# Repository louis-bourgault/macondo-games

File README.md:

# ferretboard!!!

> [!IMPORTANT]
> # PLEASE READ
> The primary documentation for this project can be found at [ferretboard.louisbourgault.com/docs](https://ferretboard.louisbourgault.com/docs). Please read from that source for organised information on software interfaces, assembly, and a more complete project overview.
> 
> This README remains the authoritative source on commands to build the firmware for the device, and also has a nice image gallery at the end.

# What is this?
Ferretboard is a simple games console, made to be easy to program and cheap to produce. Version one uses a RP2040 MCU; version two, currently in development, upgrades this to the RP2350 and changes the form factor significantly. The display is a 240x240 1.54" LCD, which is common and cost effective. It is battery powered, using a basic 3.7v LiPo.

The idea for this project, in the long term, is to be an easy introduction to programming and game development for students. The micropython sdk is editable in web, easy to get started using, and would be perfect in the long run for a classroom setting or Hack Club larger program. The upgrade to the RP2350 will make this level of software possible, with more RAM and processing power to make running complicated games within Micropython possible. 

The overall dimensions of the build are around 100x50mm for both v1 and v2, with a depth of around 20mm. The case is 3d printed.

This is made as a part of Hack Club Macondo. You can find my project at [macondo.hackclub.com/projects/1137](https://macondo.hackclub.com/projects/1137). Thank you to Hack Club for financing and helping me with this project. You can find all acknowledgements for this project at [ferretboard.louisbourgault.com/thanks](https://ferretboard.louisbourgault.com/thanks)

## Online stuff!
Docs site and main site: [ferretboard.louisbourgault.com](https://ferretboard.louisbourgault.com)
Web editor for the micropython sdk: [editor.louisbourgault.com](https://editor.louisbourgault.com)

## Project Structure
See at [ferretboard.louisbourgault.com/docs/structure](https://ferretboard.louisbourgault.com/docs/structure)

# Building Firmware
There's quite a few different firmwares at this point to build. Docs on how to do each of them:

[Original Go System](https://ferretboard.louisbourgault.com/docs/go-building)
[New micropython system (embedded into Go)](https://ferretboard.louisbourgault.com/docs/micropython-building)
[Old micropython system](https://ferretboard.louisbourgault.com/docs/oldmp-build)

To flash firmware on v2, hold down the reset button and reboot the device. On v1, manually short QSPI_SS and GND with tweezers and then reboot. The easiest access points for this are the first and last pins of the flash chip on the top side - you can just pinch the top of the flash chip, and that should do it.

Then, either use picotool over command line, or just drag the uf2 file into the RPI-RP2 volume that shows up in Finder/File Explorer/Dolphin/whatever you use.

# Assembly instructions
Assembly instructions can be found at [ferretboard.louisbourgault.com/docs/assembly](https://ferretboard.louisbourgault.com/docs/assembly).

# Gallery

The full gallery can be found at [ferretboard.louisbourgault.com/gallery](https://ferretboard.louisbourgault.com/gallery). Here is just a few sample images: 

## The micropython online editor working!

## Finished Device (v1)

## Fusion design for new version (not produced yet)

# Acknowledgements

Find all acknowledgements at [ferretboard.louisbourgault.com/thanks](https://ferretboard.louisbourgault.com/thanks)

Font file used in /software/helpers/text.go - Public Domain, [github.com/dhepper/font8x8](https://github.com/dhepper/font8x8/blob/master/font8x8_basic.h)

framebuf2 - MIT Licenced, https://github.com/peter-l5/framebuf2

codemirror v6 - MIT Licenced, https://code.haverbeke.berlin/codemirror/dev/ 

# Licensing

This project is dual-licensed:
* **Hardware:** The schematic, PCB layout, and documentation files are licensed under the [CERN Open Hardware Licence v2 - Strongly Reciprocal (CERN-OHL-S-2.0)](./mini-games/LICENSE.txt). If you modify and distribute this hardware, you must share your changes to it. 
* **Firmware/Software:** All source code is licensed under the [GNU AGPLv3](./LICENSE.txt). You can't copy and distribute a changed version of this without making your modifications public, including distribution by serving a part of this code over a network. [Even if you're Bambu Labs.](https://consumerrights.wiki/w/Bambu_Lab_cease_and_desist_against_OrcaSlicer_fork_developer)

# Looking for something?
Looking for something, like assembly instructions or something else? Please check the link up the top of this readme.

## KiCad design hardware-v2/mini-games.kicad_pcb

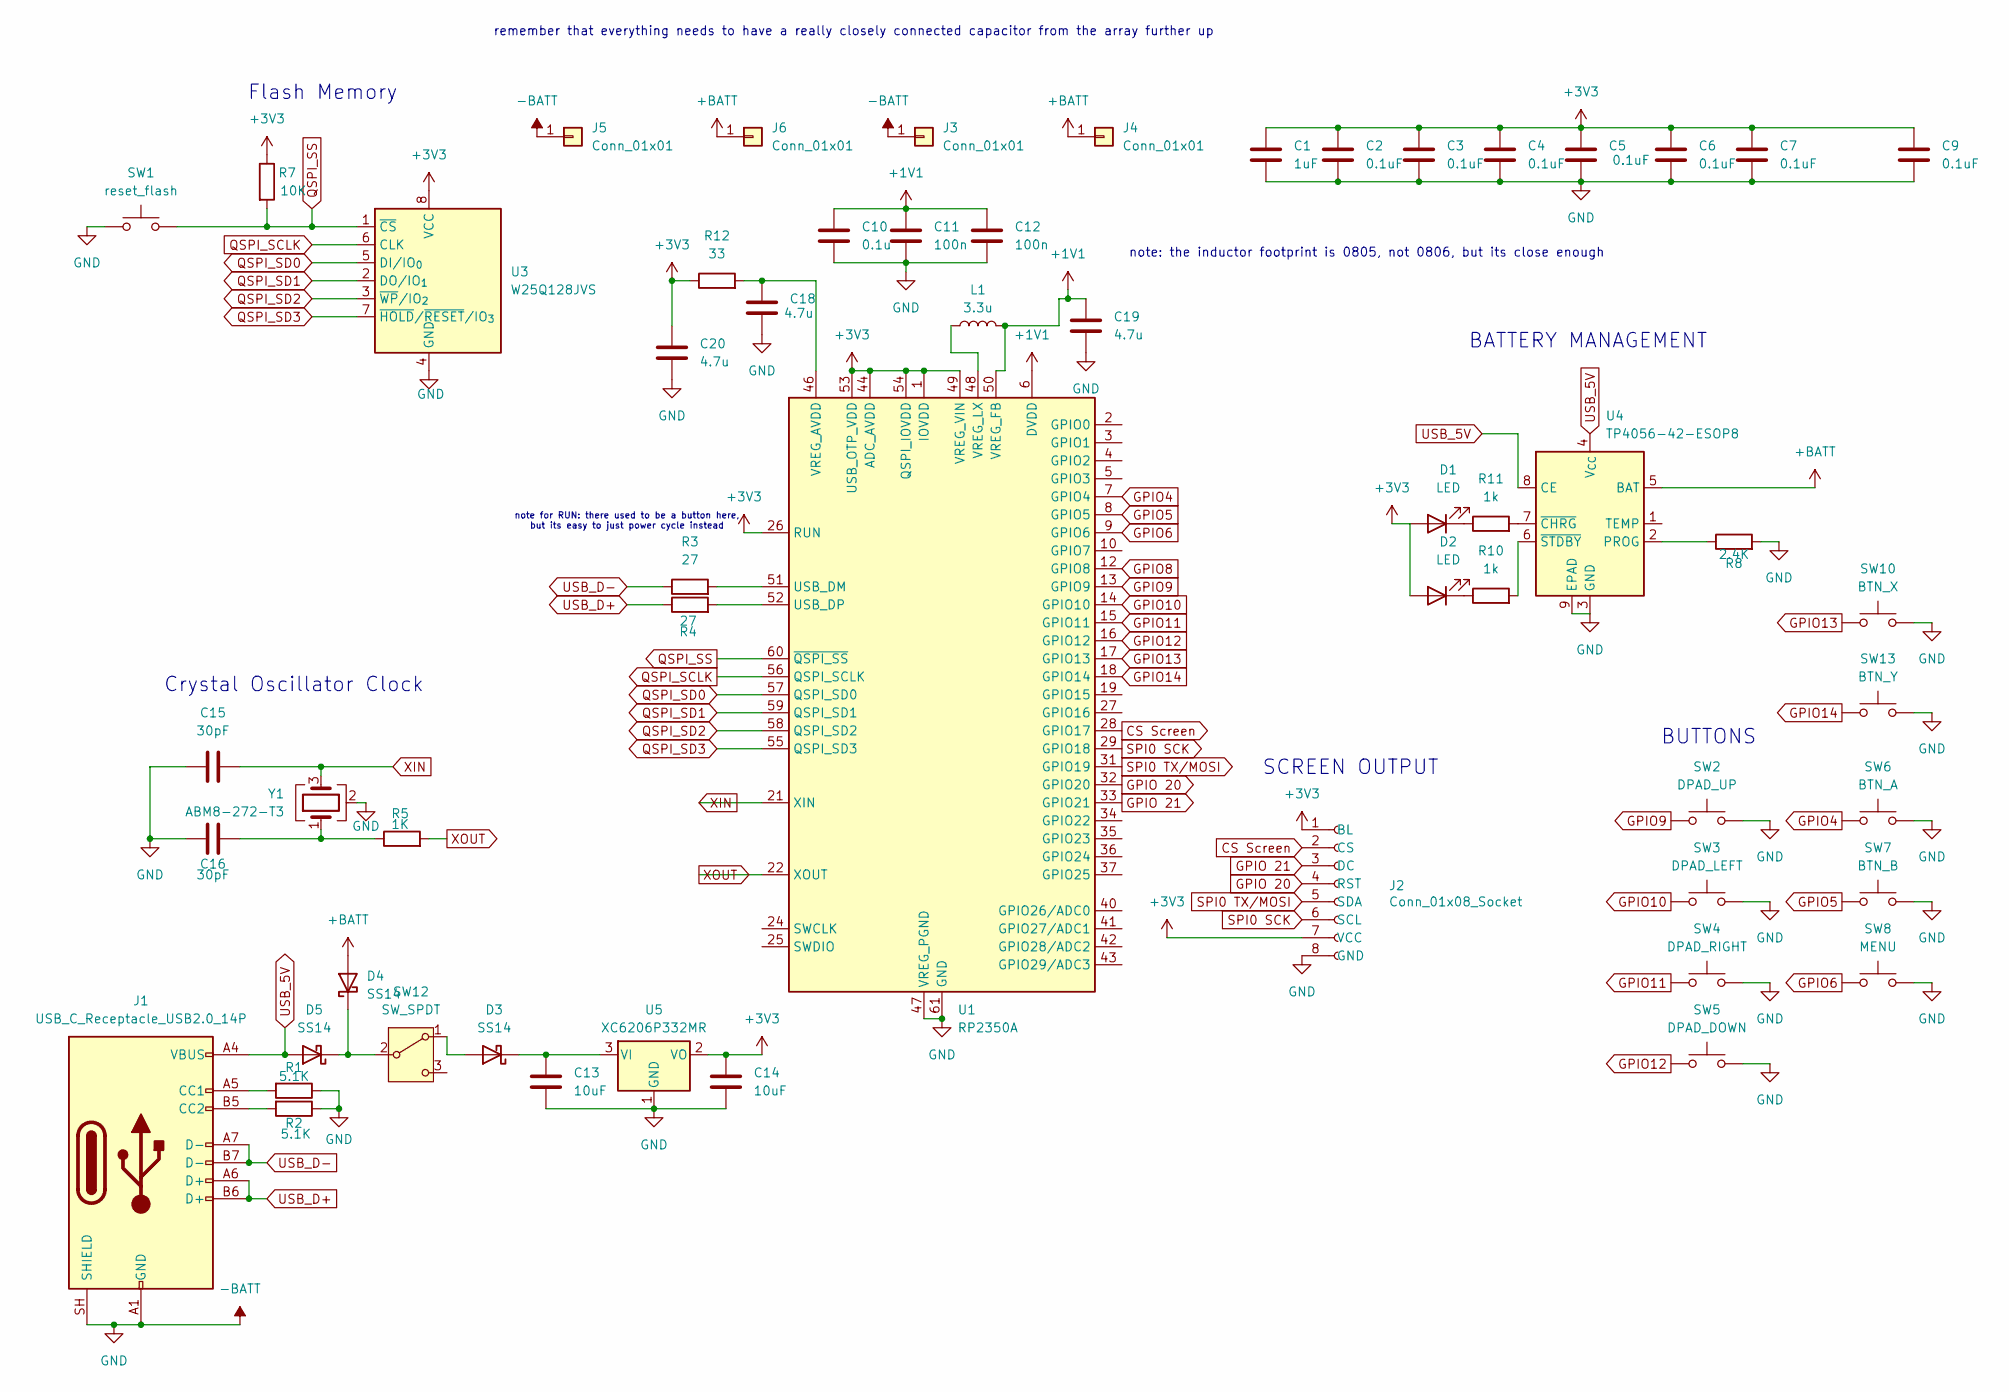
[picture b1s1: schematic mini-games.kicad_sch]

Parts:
C1: 1uF; C_0402_1005Metric
C2, C3, C4, C5, C6, C7, C9: 0.1uF; C_0402_1005Metric
C10: 0.1u; C_0402_1005Metric
C11, C12: 100n; C_0402_1005Metric
C13, C14: 10uF; C_0402_1005Metric
C15, C16: 30pF; C_0402_1005Metric
C18, C19, C20: 4.7u; C_0402_1005Metric
D1, D2: LED; LED_0603_1608Metric
D3, D4, D5: SS14; D_SOD-123
J1: USB_C_Receptacle_USB2.0_14P; USB_C_Receptacle_HRO_TYPE-C-31-M-12
J2: Conn_01x08_Socket; 1.54_ TFT Header
J3, J4, J5, J6: Conn_01x01; TestPoint_Pad_2.0x2.0mm
L1: 3.3u; L_0805_2012Metric
R1, R2: 5.1K; R_0402_1005Metric
R3, R4: 27; R_0402_1005Metric
R5: 1K; R_0402_1005Metric
R7: 10K; R_0402_1005Metric
R8: 2.4K; R_0402_1005Metric
R10, R11: 1k; R_0402_1005Metric
R12: 33; R_0402_1005Metric
SW1: reset_flash; SW_Push_SPST_NO_Alps_SKRK
SW2: DPAD_UP; SW_PUSH_6mm+6mm_Dual
SW3: DPAD_LEFT; SW_PUSH_6mm+6mm_Dual
SW4: DPAD_RIGHT; SW_PUSH_6mm+6mm_Dual
SW5: DPAD_DOWN; SW_PUSH_6mm+6mm_Dual
SW6: BTN_A; SW_PUSH_6mm+6mm_Dual
SW7: BTN_B; SW_PUSH_6mm+6mm_Dual
SW8: MENU; SW_PUSH_6mm+6mm_Dual
SW10: BTN_X; SW_PUSH_6mm+6mm_Dual
SW12: SW_SPDT; SW_SLIDE-3pin_2.54_1.2mm-hole
SW13: BTN_Y; SW_PUSH_6mm+6mm_Dual
U1: RP2350A; QFN-60-1EP_7x7mm_P0.4mm_EP3.4x3.4mm
U3: W25Q128JVS; SOIC-8_5.3x5.3mm_P1.27mm
U4: TP4056-42-ESOP8; SOIC-8-1EP_3.9x4.9mm_P1.27mm_EP2.41x3.3mm_ThermalVias
U5: XC6206P332MR; SOT-23-3
Y1: ABM8-272-T3; Crystal_SMD_3225-4Pin_3.2x2.5mm

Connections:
+1V1: C10.1, C11.1, C12.1, C19.1, L1.2, U1.6 (DVDD), U1.23 (DVDD), U1.39 (DVDD), U1.50 (VREG_FB)
+3V3: C1.1, C2.1, C3.1, C4.1, C5.1, C6.1, C7.1, C9.1, C14.1, C20.1, D1.2 (A), D2.2 (A), J2.1 (BL), J2.7 (VCC), R7.1, R12.1, U1.1 (IOVDD), U1.11 (IOVDD), U1.20 (IOVDD), U1.26 (RUN), U1.30 (IOVDD), U1.38 (IOVDD), U1.44 (ADC_AVDD), U1.45 (IOVDD), U1.49 (VREG_VIN), U1.53 (USB_OTP_VDD), U1.54 (QSPI_IOVDD), U3.8 (VCC), U5.2 (VO)
+BATT: D4.2 (A), J4.1 (Pin_1_1), J6.1 (Pin_1_1), U4.5 (BAT)
-BATT: C1.2, C2.2, C3.2, C4.2, C5.2, C6.2, C7.2, C9.2, C10.2, C11.2, C12.2, C13.2, C14.2, C15.1, C16.1, C18.2, C19.2, C20.2, J1.A1 (GND), J1.A12 (GND), J1.B1 (GND), J1.B12 (GND), J1.SH (SHIELD), J2.8 (GND), J3.1 (Pin_1_1), J5.1 (Pin_1_1), R1.1, R2.1, R8.2, SW1.1, SW2.2, SW3.2, SW4.2, SW5.2, SW6.2, SW7.2, SW8.2, SW10.2, SW13.2, U1.47 (VREG_PGND), U1.61 (GND), U3.4 (GND), U4.3 (GND), U4.9 (EPAD), U5.1 (GND), Y1.2 (G), Y1.4 (G)
CS Screen: J2.2 (CS), U1.28 (GPIO17)
GPIO4: SW6.1, U1.7 (GPIO4)
GPIO5: SW7.1, U1.8 (GPIO5)
GPIO6: SW8.1, U1.9 (GPIO6)
GPIO8: U1.12 (GPIO8)
GPIO9: SW2.1, U1.13 (GPIO9)
GPIO10: SW3.1, U1.14 (GPIO10)
GPIO11: SW4.1, U1.15 (GPIO11)
GPIO12: SW5.1, U1.16 (GPIO12)
GPIO13: SW10.1, U1.17 (GPIO13)
GPIO14: SW13.1, U1.18 (GPIO14)
GPIO 20: J2.4 (RST), U1.32 (GPIO20)
GPIO 21: J2.3 (DC), U1.33 (GPIO21)
unnamed: C16.2, R5.1, Y1.1
unnamed: D1.1 (K), R11.1
unnamed: D2.1 (K), R10.1
unnamed: D3.2 (A), SW12.1 (A)
unnamed: C13.1, D3.1 (K), U5.3 (VI)
unnamed: D4.1 (K), D5.1 (K), SW12.2 (B)
unnamed: J1.A5 (CC1), R1.2
unnamed: J1.B5 (CC2), R2.2
unnamed: R3.2, U1.51 (USB_DM)
unnamed: R4.2, U1.52 (USB_DP)
unnamed: C18.1, R12.2, U1.46 (VREG_AVDD)
unnamed: L1.1, U1.48 (VREG_LX)
unnamed: R8.1, U4.2 (PROG)
unnamed: R11.2, U4.7 (~CHRG)
unnamed: R10.2, U4.6 (~STDBY)
QSPI_SCLK: U1.56 (QSPI_SCLK), U3.6 (CLK)
QSPI_SD0: U1.57 (QSPI_SD0), U3.5 (DI/IO_{0})
QSPI_SD1: U1.59 (QSPI_SD1), U3.2 (DO/IO_{1})
QSPI_SD2: U1.58 (QSPI_SD2), U3.3 (~WP/IO_{2})
QSPI_SD3: U1.55 (QSPI_SD3), U3.7 (~HOLD/~RESET/IO_{3})
QSPI_SS: R7.2, SW1.2, U1.60 (~QSPI_SS), U3.1 (~CS)
SPI0 SCK: J2.6 (SCL), U1.29 (GPIO18)
SPI0 TX/MOSI: J2.5 (SDA), U1.31 (GPIO19)
USB_5V: D5.2 (A), J1.A4 (VBUS), J1.A9 (VBUS), J1.B4 (VBUS), J1.B9 (VBUS), U4.4 (V_{CC}), U4.8 (CE)
USB_D+: J1.A6 (D+), J1.B6 (D+), R4.1
USB_D-: J1.A7 (D-), J1.B7 (D-), R3.1
XIN: C15.2, U1.21 (XIN), Y1.3
XOUT: R5.2, U1.22 (XOUT)

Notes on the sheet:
SCREEN OUTPUT
note for RUN: there used to be a button here, but its easy to just power cycle instead
Flash Memory
BATTERY MANAGEMENT
remember that everything needs to have a really closely connected capacitor from the array further up
BUTTONS
Crystal Oscillator Clock
note: the inductor footprint is 0805, not 0806, but its close enough

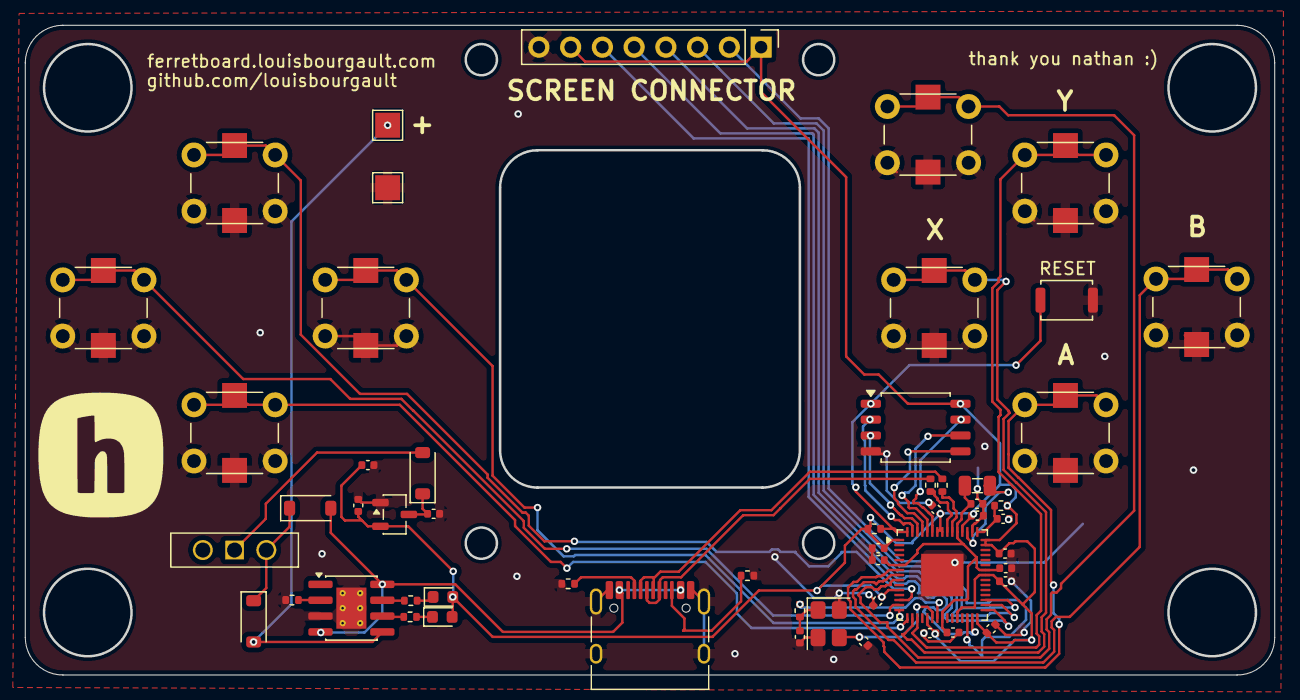
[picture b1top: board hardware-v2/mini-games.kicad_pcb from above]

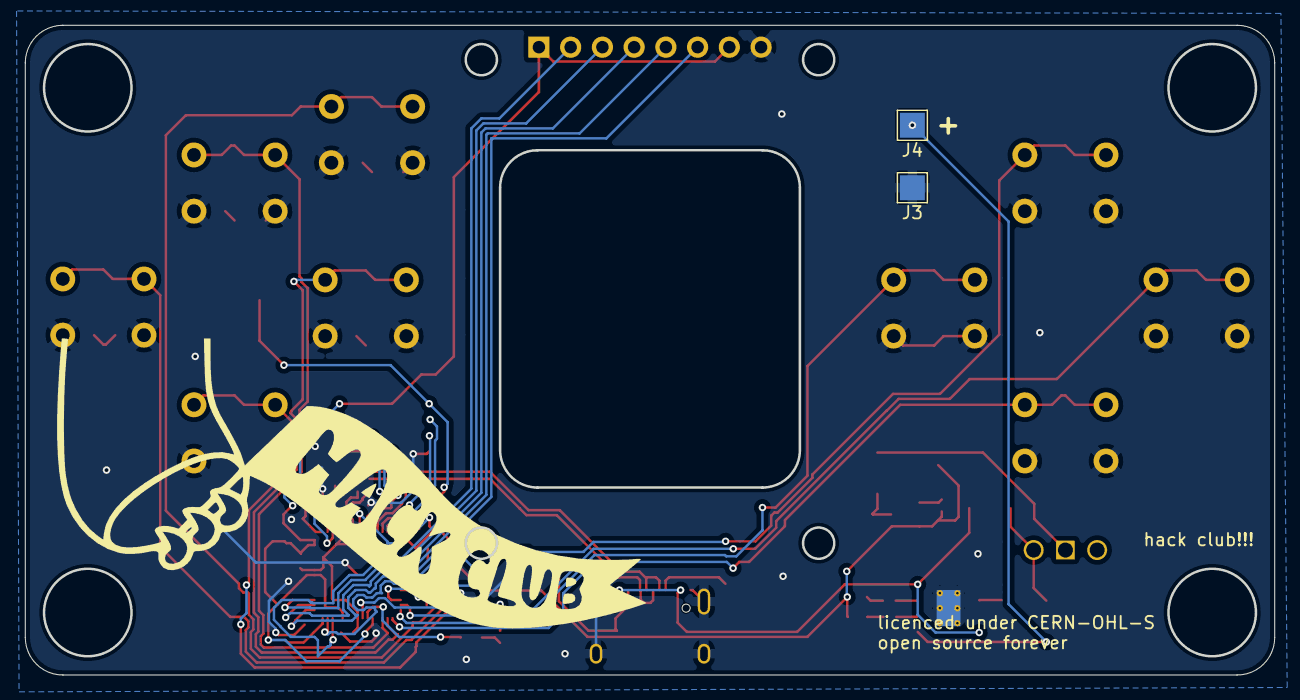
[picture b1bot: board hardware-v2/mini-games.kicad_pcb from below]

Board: 2 copper layers, 100.0 x 52.0 mm, 56 parts (2 on the bottom side), 44 nets.

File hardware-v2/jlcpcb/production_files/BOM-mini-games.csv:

Comment,Designator,Footprint,LCSC,Quantity
0.1u,C10,C_0402_1005Metric,C1525,1
0.1uF,"C2,C3,C4,C5,C6,C7,C9",C_0402_1005Metric,C1525,7
100n,"C11,C12",C_0402_1005Metric,C1525,2
10K,R7,R_0402_1005Metric,C25744,1
10uF,"C13,C14",C_0402_1005Metric,C15525,2
15pF,"C15,C16",C_0402_1005Metric,C1548,2
1K,R5,R_0402_1005Metric,C11702,1
1k,"R10,R11",R_0402_1005Metric,C11702,2
1uF,C1,C_0402_1005Metric,C52923,1
2.4K,R8,R_0402_1005Metric,C25882,1
27,"R3,R4",R_0402_1005Metric,C2909343,2
3.3u,L1,L_0806_2016Metric,C42411119,1
33,R12,R_0402_1005Metric,C25105,1
4.7u,"C18,C19,C20",C_0402_1005Metric,C23733,3
5.1K,"R1,R2",R_0402_1005Metric,C25905,2
ABM8-272-T3,Y1,Crystal_SMD_3225-4Pin_3.2x2.5mm,C20625731,1
LED,D1,LED_0603_1608Metric,C2286,1
LED,D2,LED_0603_1608Metric,C2290,1
RP2350A,U1,QFN-60-1EP_7x7mm_P0.4mm_EP3.4x3.4mm,C42411118,1
SS14,"D3,D4,D5",D_SOD-123,C49023418,3
TP4056-42-ESOP8,U4,SOIC-8-1EP_3.9x4.9mm_P1.27mm_EP2.41x3.3mm_ThermalVias,C16581,1
USB_C_Receptacle_USB2.0_14P,J1,USB_C_Receptacle_HRO_TYPE-C-31-M-12,C165948,1
W25Q128JVS,U3,SOIC-8_5.3x5.3mm_P1.27mm,C97521,1
XC6206P332MR,U5,SOT-23-3,C5446,1
reset_flash,SW1,SW_Push_SPST_NO_Alps_SKRK,C720477,1
DPAD_DOWN,SW5,SW_PUSH_6mm+6mm_Dual,,1
BTN_B,SW7,SW_PUSH_6mm+6mm_Dual,,1
BTN_A,SW6,SW_PUSH_6mm+6mm_Dual,,1
BTN_X,SW10,SW_PUSH_6mm+6mm_Dual,,1
DPAD_UP,SW2,SW_PUSH_6mm+6mm_Dual,,1
DPAD_RIGHT,SW4,SW_PUSH_6mm+6mm_Dual,,1
BTN_Y,SW13,SW_PUSH_6mm+6mm_Dual,,1
DPAD_LEFT,SW3,SW_PUSH_6mm+6mm_Dual,,1
MENU,SW8,SW_PUSH_6mm+6mm_Dual,,1
Conn_01x08_Socket,J2,1.54_ TFT Header,,1
Conn_01x01,J4,TestPoint_Pad_2.0x2.0mm,,1
SW_SPDT,SW12,SW_SLIDE-3pin_2.54_1.2mm-hole,,1
Conn_01x01,J3,TestPoint_Pad_2.0x2.0mm,,1
Conn_01x01,J5,TestPoint_Pad_2.0x2.0mm,,1
Conn_01x01,J6,TestPoint_Pad_2.0x2.0mm,,1

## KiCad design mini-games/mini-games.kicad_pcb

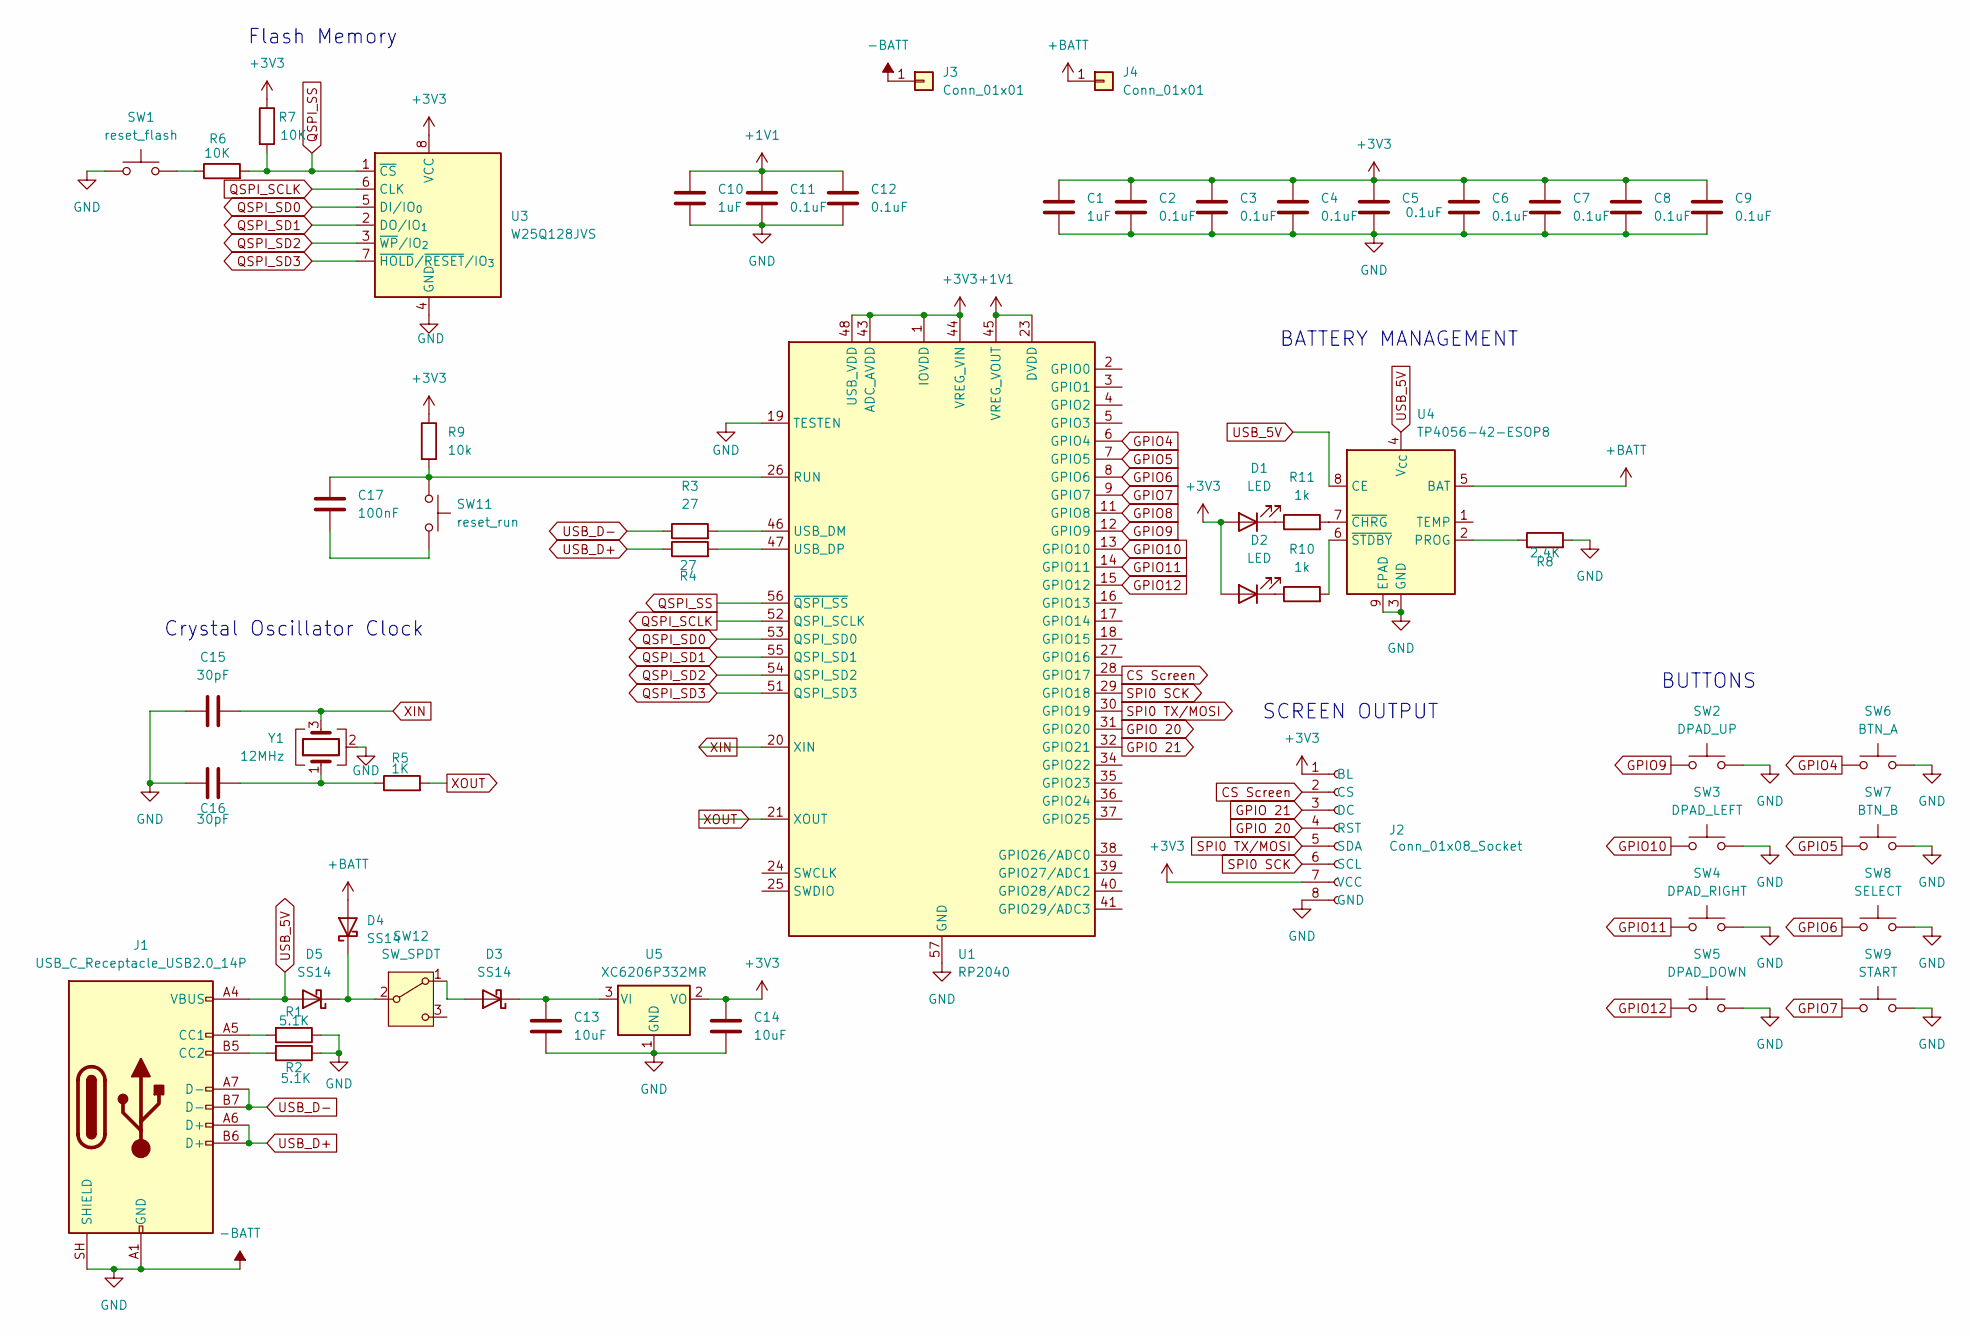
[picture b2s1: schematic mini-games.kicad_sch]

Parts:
C1, C10: 1uF; C_0402_1005Metric
C2, C3, C4, C5, C6, C7, C8, C9, C11, C12: 0.1uF; C_0402_1005Metric
C13, C14: 10uF; C_0402_1005Metric
C15, C16: 30pF; C_0402_1005Metric
C17: 100nF; C_0402_1005Metric
D1, D2: LED; LED_0603_1608Metric
D3, D4, D5: SS14; D_SOD-123
J1: USB_C_Receptacle_USB2.0_14P; USB_C_Receptacle_HRO_TYPE-C-31-M-12
J2: Conn_01x08_Socket; PinHeader_1x08_P2.54mm_Vertical
J3, J4: Conn_01x01; TestPoint_Pad_2.0x2.0mm
R1, R2: 5.1K; R_0402_1005Metric
R3, R4: 27; R_0402_1005Metric
R5: 1K; R_0402_1005Metric
R6, R7: 10K; R_0402_1005Metric
R8: 2.4K; R_0402_1005Metric
R9: 10k; R_0402_1005Metric
R10, R11: 1k; R_0402_1005Metric
SW1: reset_flash; SW_Push_SPST_NO_Alps_SKRK
SW2: DPAD_UP; SW_PUSH_6mm
SW3: DPAD_LEFT; SW_PUSH_6mm
SW4: DPAD_RIGHT; SW_PUSH_6mm
SW5: DPAD_DOWN; SW_PUSH_6mm
SW6: BTN_A; SW_PUSH_6mm
SW7: BTN_B; SW_PUSH_6mm
SW8: SELECT; SW_Push_SPST_NO_Alps_SKRK
SW9: START; SW_Push_SPST_NO_Alps_SKRK
SW11: reset_run; SW_Push_SPST_NO_Alps_SKRK
SW12: SW_SPDT; SW_SPDT_Shouhan_MSK12C02
U1: RP2040; QFN-56-1EP_7x7mm_P0.4mm_EP3.2x3.2mm
U3: W25Q128JVS; SOIC-8_5.3x5.3mm_P1.27mm
U4: TP4056-42-ESOP8; SOIC-8-1EP_3.9x4.9mm_P1.27mm_EP2.41x3.3mm_ThermalVias
U5: XC6206P332MR; SOT-23-3
Y1: 12MHz; Crystal_SMD_3225-4Pin_3.2x2.5mm

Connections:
+1V1: C10.1, C11.1, C12.1, U1.23 (DVDD), U1.45 (VREG_VOUT), U1.50 (DVDD)
+3V3: C1.1, C2.1, C3.1, C4.1, C5.1, C6.1, C7.1, C8.1, C9.1, C14.1, D1.2 (A), D2.2 (A), J2.1 (BL), J2.7 (VCC), R7.1, R9.1, U1.1 (IOVDD), U1.10 (IOVDD), U1.22 (IOVDD), U1.33 (IOVDD), U1.42 (IOVDD), U1.43 (ADC_AVDD), U1.44 (VREG_VIN), U1.48 (USB_VDD), U1.49 (IOVDD), U3.8 (VCC), U5.2 (VO)
+BATT: D4.2 (A), J4.1 (Pin_1_1), U4.5 (BAT)
-BATT: C1.2, C2.2, C3.2, C4.2, C5.2, C6.2, C7.2, C8.2, C9.2, C10.2, C11.2, C12.2, C13.2, C14.2, C15.1, C16.1, J1.A1 (GND), J1.A12 (GND), J1.B1 (GND), J1.B12 (GND), J1.SH (SHIELD), J2.8 (GND), J3.1 (Pin_1_1), R1.1, R2.1, R8.2, SW1.1, SW2.2, SW3.2, SW4.2, SW5.2, SW6.2, SW7.2, SW8.2, SW9.2, SW12.SH, U1.19 (TESTEN), U1.57 (GND), U3.4 (GND), U4.3 (GND), U4.9 (EPAD), U5.1 (GND), Y1.2 (G), Y1.4 (G)
CS Screen: J2.2 (CS), U1.28 (GPIO17)
GPIO4: SW6.1, U1.6 (GPIO4)
GPIO5: SW7.1, U1.7 (GPIO5)
GPIO6: SW8.1, U1.8 (GPIO6)
GPIO7: SW9.1, U1.9 (GPIO7)
GPIO8: U1.11 (GPIO8)
GPIO9: SW2.1, U1.12 (GPIO9)
GPIO10: SW3.1, U1.13 (GPIO10)
GPIO11: SW4.1, U1.14 (GPIO11)
GPIO12: SW5.1, U1.15 (GPIO12)
GPIO 20: J2.4 (RST), U1.31 (GPIO20)
GPIO 21: J2.3 (DC), U1.32 (GPIO21)
unnamed: C16.2, R5.1, Y1.1
unnamed: C17.2, SW11.2
unnamed: D1.1 (K), R11.1
unnamed: D2.1 (K), R10.1
unnamed: D3.2 (A), SW12.1 (A)
unnamed: C13.1, D3.1 (K), U5.3 (VI)
unnamed: D4.1 (K), D5.1 (K), SW12.2 (B)
unnamed: J1.A5 (CC1), R1.2
unnamed: J1.B5 (CC2), R2.2
unnamed: R6.1, SW1.2
unnamed: C17.1, R9.2, SW11.1, U1.26 (RUN)
unnamed: R3.2, U1.46 (USB_DM)
unnamed: R4.2, U1.47 (USB_DP)
unnamed: R8.1, U4.2 (PROG)
unnamed: R11.2, U4.7 (~CHRG)
unnamed: R10.2, U4.6 (~STDBY)
QSPI_SCLK: U1.52 (QSPI_SCLK), U3.6 (CLK)
QSPI_SD0: U1.53 (QSPI_SD0), U3.5 (DI/IO_{0})
QSPI_SD1: U1.55 (QSPI_SD1), U3.2 (DO/IO_{1})
QSPI_SD2: U1.54 (QSPI_SD2), U3.3 (~WP/IO_{2})
QSPI_SD3: U1.51 (QSPI_SD3), U3.7 (~HOLD/~RESET/IO_{3})
QSPI_SS: R6.2, R7.2, U1.56 (~QSPI_SS), U3.1 (~CS)
SPI0 SCK: J2.6 (SCL), U1.29 (GPIO18)
SPI0 TX/MOSI: J2.5 (SDA), U1.30 (GPIO19)
USB_5V: D5.2 (A), J1.A4 (VBUS), J1.A9 (VBUS), J1.B4 (VBUS), J1.B9 (VBUS), U4.4 (V_{CC}), U4.8 (CE)
USB_D+: J1.A6 (D+), J1.B6 (D+), R4.1
USB_D-: J1.A7 (D-), J1.B7 (D-), R3.1
XIN: C15.2, U1.20 (XIN), Y1.3
XOUT: R5.2, U1.21 (XOUT)

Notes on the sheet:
SCREEN OUTPUT
Flash Memory
BATTERY MANAGEMENT
BUTTONS
Crystal Oscillator Clock

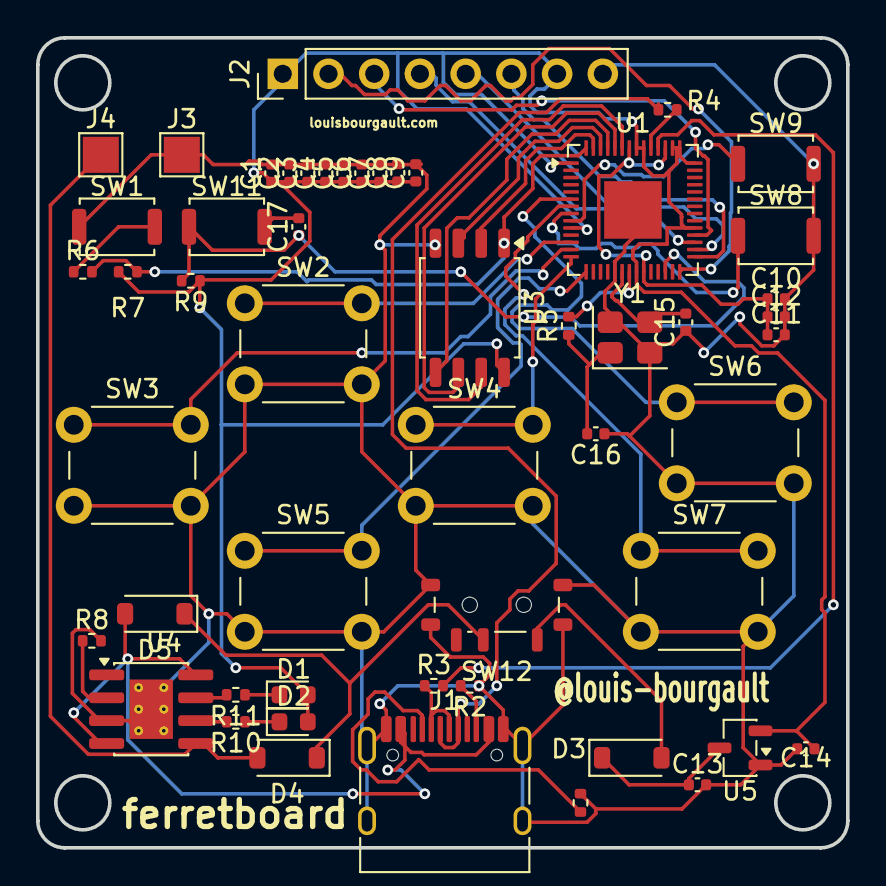
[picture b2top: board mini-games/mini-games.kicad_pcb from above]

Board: 2 copper layers, 45.0 x 45.0 mm, 53 parts (0 on the bottom side), 44 nets.

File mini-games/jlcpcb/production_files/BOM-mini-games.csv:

Comment,Designator,Footprint,LCSC,Quantity
0.1uF,"C11,C12,C2,C3,C4,C5,C6,C7,C8,C9",C_0402_1005Metric,C1525,10
100nF,C17,C_0402_1005Metric,C1525,1
10K,"R6,R7",R_0402_1005Metric,C25744,2
10k,R9,R_0402_1005Metric,C25744,1
10uF,"C13,C14",C_0402_1005Metric,C15525,2
12MHz,Y1,Crystal_SMD_3225-4Pin_3.2x2.5mm,C9002,1
1K,R5,R_0402_1005Metric,C11702,1
1k,"R10,R11",R_0402_1005Metric,C11702,2
1uF,"C1,C10",C_0402_1005Metric,C52923,2
2.4K,R8,R_0402_1005Metric,C25882,1
27,"R3,R4",R_0402_1005Metric,C25100,2
30pF,"C15,C16",C_0402_1005Metric,C1570,2
5.1K,"R1,R2",R_0402_1005Metric,C25905,2
LED,D1,LED_0603_1608Metric,C2286,1
LED,D2,LED_0603_1608Metric,C2290,1
POWER,SW10,SW_DIP_SPSTx01_Slide_Copal_CHS-01B_W7.62mm_P1.27mm,C3312309,1
RP2040,U1,QFN-56-1EP_7x7mm_P0.4mm_EP3.2x3.2mm,C2040,1
SELECT,SW8,SW_Push_SPST_NO_Alps_SKRK,C720477,1
SS14,"D3,D4,D5",D_SOD-123,C2480,3
START,SW9,SW_Push_SPST_NO_Alps_SKRK,C720477,1
TP4056-42-ESOP8,U4,SOIC-8-1EP_3.9x4.9mm_P1.27mm_EP2.41x3.3mm_ThermalVias,C16581,1
USB_C_Receptacle_USB2.0_14P,J1,USB_C_Receptacle_HRO_TYPE-C-31-M-12,C165948,1
W25Q128JVS,U3,SOIC-8_5.3x5.3mm_P1.27mm,C97521,1
XC6206P332MR,U5,SOT-23-3,C5446,1
reset_flash,SW1,SW_Push_SPST_NO_Alps_SKRK,C720477,1
reset_run,SW11,SW_Push_SPST_NO_Alps_SKRK,C720477,1
DPAD_DOWN,SW5,SW_PUSH_6mm,,1
DPAD_LEFT,SW3,SW_PUSH_6mm,,1
DPAD_UP,SW2,SW_PUSH_6mm,,1
DPAD_RIGHT,SW4,SW_PUSH_6mm,,1
BTN_B,SW7,SW_PUSH_6mm,,1
Conn_01x01,J4,TestPoint_Pad_2.0x2.0mm,,1
Conn_01x01,J3,TestPoint_Pad_2.0x2.0mm,,1
BTN_A,SW6,SW_PUSH_6mm,,1
Conn_01x08_Socket,J2,PinHeader_1x08_P2.54mm_Vertical,,1

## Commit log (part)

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2026-05-04 added files
2026-05-04 add readme
2026-05-07 finish schematic, start pcb
2026-05-07 edit pcb, layout things and change footprints yet again
2026-05-09 added gitignore
2026-05-09 categorised parts on pcb; changed one or two footprints, general improvements
2026-05-09 added backup files
2026-05-10 Finalised feature placements and routed PCB. Yet to fix errors given by DRC
2026-05-10 fixed drc critical problems
2026-05-10 added text
2026-05-11 updated, fixed more errors, ready for review i beleive!
2026-05-11 sorry, need to add this
2026-05-12 add files for software and production (not current production files)
2026-05-14 updated schematic, and assigned JLC LPSC numbers in project.db ready for production. Changed some parts and footprints in order to use basic parts on JLC and avoid fees.
2026-05-14 finished pcb and exported fabrication outputs in mini-games/jlcpcb/production_files
2026-05-15 software stuff! Made wasm work, and set up interface for other stuff
2026-05-16 added an input system, and made a looping system with framerates (locked to 60 for now)
2026-05-16 made the website nice, fixed the input system, made a basic demo - really boring demo though, but at least it's there
2026-05-17 added case files and made a copy of production files in /production
2026-05-17 perhaps the most boring video game ever made has been created. Behold its magnificence. Behold it's beauty. i will improve this later trust
2026-05-17 updated readme and made everything ready to submit
2026-05-17 banner!
2026-05-26 i forgot to add a step fie earlier. This is from kicad. nothing was changed, just different format
2026-05-31 removed NC connection to gnd, changed switch, ready for production!
2026-06-01 bug fixes
2026-06-02 navigating between games is working
2026-06-03 things, a basic switching between games system is in place. Anything to procrastnate actually having to code one smh
2026-06-03 optimised input system; implemented snake
2026-06-03 improved readme
2026-06-04 added sprite system
2026-06-05 logging, images and flappy bird!
2026-06-05 added the mandelbrot weird stuff
2026-06-07 chess is decent i think??
2026-06-08 Improved the menu, made it look nice
2026-06-08 docs site startting
2026-06-08 docs stuff
2026-06-09 lets go gambling
2026-06-10 started tetris, fixed crash in blackjack
2026-06-10 started tetris, still lots to do.
2026-06-11 icons and stuff
2026-06-12 docs have been started
2026-06-12 removed some of the stupid annoying files like .history and ds-store
2026-06-12 things? idk
2026-06-12 fighting git
2026-06-12 fighting git more??
2026-06-12 more docs
2026-06-19 seeded randomness
2026-06-19 fixed some of the display sending stuff
2026-06-19 documented game interface, removed old helper script
2026-06-20 feat: it works.
2026-06-20 added physical device to website, fixed minor things in docs
2026-06-20 docs: remove wip label from docs
2026-06-20 added more information on controls for different games
2026-06-20 fix: actual favicon
2026-06-20 made tetris speed up
2026-06-21 licence and readme

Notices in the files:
hardware-v2/mini-games.kicad_pcb:
licenced under CERN-OHL-S
